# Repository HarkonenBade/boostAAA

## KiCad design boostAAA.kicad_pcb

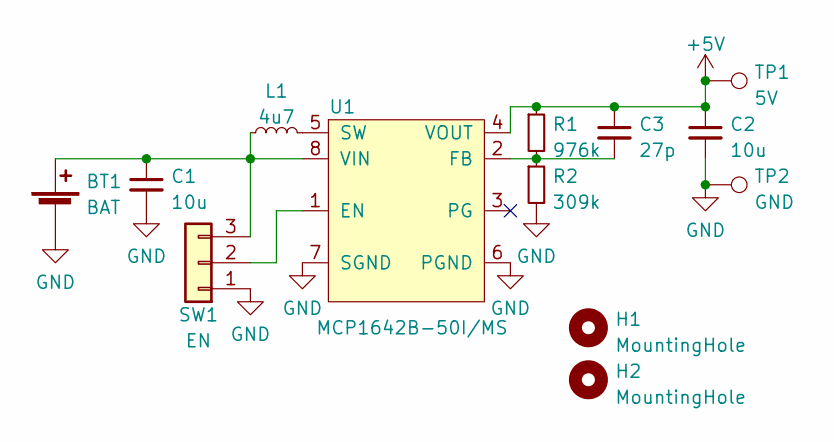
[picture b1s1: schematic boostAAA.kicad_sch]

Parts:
BT1: BAT; BatteryHolder_Keystone_2466_1xAAA; Farnell 3126578
C1, C2: 10u; C_0805_2012Metric; Farnell 3013456
C3: 27p; C_0603_1608Metric; Farnell 3013456
H1, H2: MountingHole; MountingHole_3.2mm_M3
L1: 4u7; L_Vishay_IFSC-1515AH_4x4x1.8mm; Farnell 2771305
R1: 976k; R_0603_1608Metric
R2: 309k; R_0603_1608Metric
SW1: EN; EN_SW
TP1: 5V; TestPoint_Pad_3.0x3.0mm
TP2: GND; TestPoint_Pad_3.0x3.0mm
U1: MCP1642B-50I/MS; MSOP-8_3x3mm_P0.65mm; Farnell 2920811

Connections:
+5V: C2.1, C3.1, R1.1, TP1.1, U1.4 (VOUT)
GND: BT1.2 (-), C1.2, C2.2, R2.2, SW1.1, TP2.1, U1.6 (PGND), U1.7 (SGND)
unnamed: BT1.1 (+), C1.1, L1.1, SW1.3, U1.8 (VIN)
unnamed: C3.2, R1.2, R2.1, U1.2 (FB)
unnamed: L1.2, U1.5 (SW)
unnamed: SW1.2, U1.1 (EN)

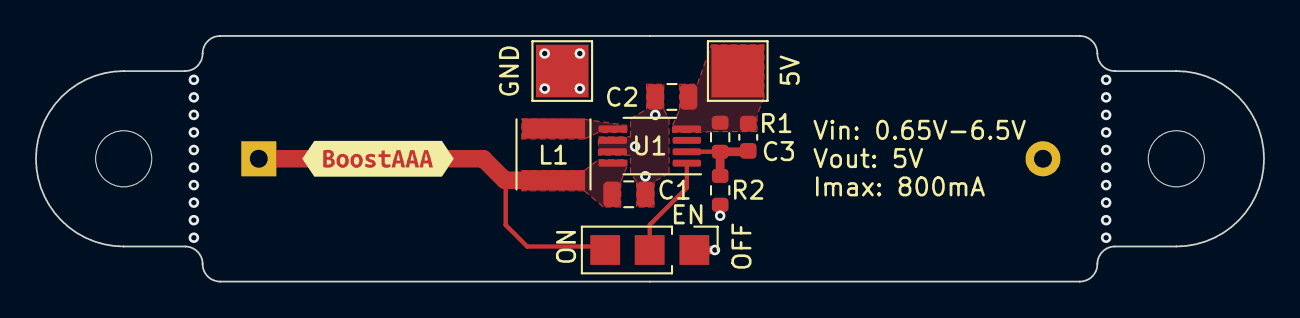
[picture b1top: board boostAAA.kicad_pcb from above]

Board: 2 copper layers, 70.0 x 14.0 mm, 14 parts (1 on the bottom side), 6 nets.

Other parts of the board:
kibuzzard-6259CC62: G***; kibuzzard-6259CC62

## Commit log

2022-04-15 Init
2022-04-15 Panel Tweak
2022-04-17 Various final tweaks
2022-05-04 Updated version to use autogen for library symbols and to allow for the use of adjustable as well as fixed versions of the regulator chip.
2022-05-04 Gerbers for both single board and panels
2022-05-22 LCSC Part Numbers and BOM
